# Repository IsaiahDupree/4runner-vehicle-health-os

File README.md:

# 4Runner Vehicle Health OS

Local-first, explainable vehicle-health and maintenance software for a 2005 Toyota 4Runner.

The project has two immutable source baselines: [Vehicle Health OS PRD v0.1](docs/prd/2005_Toyota_4Runner_Vehicle_Health_OS_PRD_v0.1.docx) and [Telemetry Build Master Spec v1](docs/prd/4Runner_Telemetry_Build_Master_Spec.docx). Their joined authority and unique requirement namespaces are defined in the [master project specification](docs/prd/MASTER-PROJECT-SPEC.md). The later [focused A/C telemetry source record](docs/prd/AC-TELEMETRY-SOURCE.md) controls the A/C node where it is more specific. The governing invariant is:

> raw observation -> decoded signal -> feature -> versioned equation -> calculation run -> finding -> recommendation -> service/inspection -> new lifecycle baseline

No derived value is authoritative unless that lineage can be reconstructed.

## Current baseline

E0 plus the first native iOS control slice are implemented here:

- stable typed domain IDs;
- versioned JSON Schemas for evidence, signals, captures, equations, calculations, and AI claims;
- a protobuf source contract and fixed transport-frame decision for mobile/ESP32 interoperability;
- deterministic simulator capture bundles with hashes and manifests;
- an A/C bench-sweep capture/replay path, A/C node telemetry and POST contracts, and evidence-bound pressure-lift, pressure-ratio, and vent-delta calculations;
- offline replay with integrity, sequence, timestamp, and schema validation;
- a versioned passive-CAN discovery analyzer that reports acquisition facts, sampling coverage,
  raw activity, checksum candidates, and correlations without assigning unverified vehicle meanings;
- a source-pinned 2005 4Runner passive-CAN hypothesis pack and real-corpus evaluator that exposes
  candidate fields, conflicting transforms, limitations, and validation gates while keeping the
  accepted signal count at zero;
- an immutable eight-session/5,176-record real-CAN replay corpus with SHA-256 provenance, clean and
  faulted live/history reconstruction, and production-decoder load tests in Python, Swift, and Kotlin;
- self-resynchronizing mobile stream decoders that surface discarded/corrupt transport bytes and
  recover later valid frames without converting communication faults into vehicle-health claims;
- a canonical 15-scenario real-evidence reliability matrix covering 20-cycle soak, MTU churn,
  bursts, duplicates, loss, corruption, reordering, stale link epochs, reconnects, modeled
  supervision timeout, queue overrun, bounded memory, and mixed interference, with aligned Swift
  transport tests and a full Kotlin/on-head-unit implementation;
- per-ECU SAE J1979 supported-PID enumeration, pinned standard read-only value decoding, and an
  iPhone/Android passive-response path that cannot substitute zero for unavailable evidence;
- synchronized Techstream/reference capture plus a candidate-only analyzer for `0x2C4`, `0x025`,
  and `0x2C1` raw fields;
- deterministic passive-CAN archive offload/reload plus an iOS multi-session research chart that
  plots retained evidence, pins pack/hash/validation lineage, and fails closed across app restarts;
- a durable iPhone private-evidence outbox and authenticated append-only receiver/agent claim queue;
- CI checks for schema validity and deterministic replay;
- a Swift 6 core with CRC32C framing, guarded discovery plans, signed firmware verification, OTA preflight, and AI evidence handoff;
- a buildable native SwiftUI app with handshake-verified CoreBluetooth restoration,
  encrypted-bond reconnection, WiCAN factory detection, gateway health, signed semantic experiments,
  private-network OTA, and evidence export;
- a local-first technician diagnostic-case workspace with immutable revisions, typed evidence and
  hypotheses, hash-verified private attachments, verification/void history, and deterministic
  privacy-selected draft reports that cannot mutate canonical maintenance history;
- a signed public Release Hub consumed by iPhone and Android for target-aware Android, OBD ESP32,
  and A/C recovery artifact discovery and verified staging;
- a public WiCAN Pro ESP32-S3 firmware fork with passive/listen-only enforcement, framed BLE health reporting, OTA A/B partitions, and rollback self-tests;
- a physically targeted classic-ESP32/MrDIY firmware with bonded BLE health, passive CAN, persistent
  evidence, A/B rollback, a release-default-off status SoftAP, and explicitly activated signed Wi-Fi
  OTA;
- a backup-first public Web Serial provisioner with target detection, full-flash recovery download, release hashing, installation, and same-capacity restore;
- explicit iOS, legacy Android, gateway firmware, and added-sensor hardware boundaries.

No target-vehicle PID, threshold, service interval, or trim-specific constant is invented in this baseline. Those enter only through independently validated, versioned Vehicle Signal and Configuration Packs.

## Quick start

Requires Python 3.12 or newer.

```bash
python3 -m venv .venv
.venv/bin/python -m pip install -e './tooling[test]'
.venv/bin/vhos contracts check
.venv/bin/vhos simulate --scenario cold-start-idle --output build/captures/cold-start-idle
.venv/bin/vhos validate-bundle build/captures/cold-start-idle
.venv/bin/vhos replay build/captures/cold-start-idle
.venv/bin/vhos simulate --scenario ac-bench-sweep --output build/captures/ac-bench-sweep
.venv/bin/vhos validate-bundle build/captures/ac-bench-sweep
.venv/bin/vhos calculate-ac build/captures/ac-bench-sweep
.venv/bin/vhos discover-can path/to/passive-can-recent-logs.ndjson \
  --output build/can-discovery.report.json
.venv/bin/vhos evaluate-can-hypotheses \
  test-replay/real-can-2026-08-18/sessions \
  --output build/can-signal-hypotheses.report.json
.venv/bin/vhos validate-can-replay-corpus test-replay/real-can-2026-08-18
.venv/bin/vhos replay-can-corpus test-replay/real-can-2026-08-18 \
  --mode live --repeat 20 --fault clean
.venv/bin/vhos replay-can-corpus test-replay/real-can-2026-08-18 \
  --mode history --fault drop-fragment --fault-interval 257
.venv/bin/vhos test-link-reliability test-replay/real-can-2026-08-18 \
  --soak-cycles 20 --output build/link-reliability-matrix.json
.venv/bin/vhos decode-j1979 path/to/j1979-responses.ndjson \
  --supported-output build/j1979-supported.json \
  --samples-output build/j1979-standard-samples.ndjson
.venv/bin/vhos correlate-can-reference \
  --can path/to/passive-can.ndjson \
  --reference path/to/synchronized-reference-samples.csv \
  --output build/can-reference-candidates.json
.venv/bin/python -m pytest
```

The simulator namespace is deliberately separate from live vehicle data. It creates deterministic engineering evidence for automated tests; it never represents itself as a Toyota measurement.

## Gateway provisioning

- Signed release catalog: [VHOS Release Hub](https://github.com/IsaiahDupree/4runner-vhos-release-hub/releases/latest)
- Public installer: [VHOS Gateway Provisioner](https://vhos-gateway-provisioner.isaiahdupree.chatgpt.site)
- Public firmware source: [IsaiahDupree/4runner-vhos-firmware](https://github.com/IsaiahDupree/4runner-vhos-firmware)
- Development release and recovery evidence: [v0.1.0-dev.1](https://github.com/IsaiahDupree/4runner-vhos-firmware/releases/tag/v0.1.0-dev.1)
- Hardware/software baseline: [recommended hardware](docs/hardware/RECOMMENDED-HARDWARE.md) and [software baseline](docs/hardware/SOFTWARE-BASELINE.md)
- SoftAP incident and default-off activation decision: [2026-08-16 record](docs/development/ESP32-SOFTAP-ACTIVATION-INCIDENT-2026-08-16.md)
- One-command pre-car contracts/build/reset/app-death suite and true-power boundary: [BLE fault-injection plan](docs/development/BLE-FAULT-INJECTION-TEST-PLAN.md)
- Capture-export disconnect and dev28/dev29 recovery: [2026-08-18 incident](docs/development/BLE-CAPTURE-SYNC-DISCONNECT-INCIDENT-2026-08-18.md)

The first installation and recovery path uses a desktop Chrome or Edge browser, USB-C data, and Web
Serial. The browser requires a full-flash backup before it installs the merged image. The iPhone OTA
software path is implemented, but vehicle installation remains locked until deterministic PARKED
and gateway-supply evidence plus the physical backup/upload/power-loss/rollback/restore matrix pass.
See [iPhone to ESP32 Wi-Fi OTA](docs/development/IPHONE-TO-ESP32-WIFI-OTA.md).
The stable device labels and separation from transport identifiers are defined in
[the device naming contract](docs/development/DEVICE-NAMING-CONTRACT.md).

## Repository map

| Path | Responsibility |
| --- | --- |
| `docs/prd/` | Immutable product baseline and source integrity record |
| `docs/architecture/decisions/` | Accepted technical decisions and invariants |
| `contracts/jsonschema/v1/` | Authoritative serialized domain contracts |
| `contracts/proto/v1/` | Mobile/ESP32 payload source contract |
| `equations/v1/` | Immutable A/C equation definitions with applicability and truth boundaries |
| `tooling/` | Contract validator, simulator, bundle writer, and replay engine |
| `tests/` | Contract, determinism, corruption, ordering, and replay tests |
| `test-replay/` | Immutable real-capture corpora and cross-platform replay provenance |
| `ios/` | Native iOS app, portable Swift core, and deterministic XcodeGen project |
| `web-flasher/` | Public backup-first ESP32-S3 installer and recovery UI |
| `android/` | Preserved original Android module boundary; not the primary client after ADR-0003 |
| `firmware/` | Shared ESP32 component boundaries and read-only safety policy |
| `vehicle-signal-packs/` | Accepted signal/configuration packs plus separately contracted, discovery-only hypothesis packs that cannot feed owner health |

Related public repositories keep runtime ownership separate: Android head unit
[`4runner-vhos-android`](https://github.com/IsaiahDupree/4runner-vhos-android) ([download the current `0.1.0-dev.16` APK](https://github.com/IsaiahDupree/4runner-vhos-android/releases/download/android-v0.1.0-dev.16/app-debug.apk)), OBD firmware
[`4runner-vhos-firmware`](https://github.com/IsaiahDupree/4runner-vhos-firmware), A/C firmware
[`4runner-ac-telemetry-node`](https://github.com/IsaiahDupree/4runner-ac-telemetry-node), and the
signed catalog/portal [`4runner-vhos-release-hub`](https://github.com/IsaiahDupree/4runner-vhos-release-hub).

## Development order

1. E1: iOS append-only local truth store and lifecycle ledger; the gateway contract client is now scaffolded.
2. E2: physically verify the published WiCAN Pro VHOS foundation, then add passive capture and constrained discovery without widening the transmit boundary.
3. E3: iOS ingest, reconnect/deduplication, raw persistence, and replay adapter.
4. E4: verified generic OBD baseline plus target-vehicle signal discovery and validation.
5. E5/E6: maintenance schedule and equation/lineage engines before owner-facing scoring.

See [E0 implementation record](docs/delivery/E0-IMPLEMENTATION.md) for the exact backlog and acceptance mapping.
The current saved-vehicle evidence and strict UI interpretation boundary are recorded in the
[CAN discovery display baseline](docs/development/CAN-DISCOVERY-DISPLAY-BASELINE-2026-08-18.md).
The device-free sustained-load, corruption, fragmentation, disconnect, and Android historical
replay workflow is recorded in
[the real-CAN replay record](docs/development/REAL-CAN-REPLAY-AND-LOAD-TESTING-2026-08-18.md).
The 15-condition cross-device impairment matrix, acceptance budgets, Android reliability UI, and
remaining hardware-in-loop gates are recorded in
[the cross-device reliability lab](docs/development/CROSS-DEVICE-RELIABILITY-LAB-2026-08-18.md).
The supported-PID, synchronized Toyota-reference, and private-outbox implementation is recorded in
[the August 18 J1979/evidence delivery](docs/development/J1979-REFERENCE-VALIDATION-AND-PRIVATE-OUTBOX-2026-08-18.md).
The current source-pinned Toyota signal candidates, corpus results, interpretation boundaries, and
minimum validation session are recorded in
[the CAN signal interpretation record](docs/development/CAN-SIGNAL-INTERPRETATION-2026-08-18.md).
The latest iPhone-export verification, primary-source research update, candidate ranking, Android
display boundary, and next labeled-capture procedure are recorded in
[the 2026-08-20 CAN evidence and research update](docs/development/CAN-EVIDENCE-RESEARCH-UPDATE-2026-08-20.md).
The real-evidence iPhone chart, fresh-session archive reload gate, exact candidate fields, and
owner-health authority lock are recorded in
[the iOS retained CAN research implementation](docs/development/IOS-RETAINED-CAN-RESEARCH-GRAPHS-2026-08-20.md).
The play/pause/scrub/speed/loop transport, progressive exact-point graph, session-boundary display,
and real multi-session acceptance suite are recorded in
[the iOS retained CAN playback lab](docs/development/IOS-RETAINED-CAN-PLAYBACK-LAB-2026-08-20.md).

The authority-separated physical-unit candidates, derived statistics, rotational comparison, and
cross-platform presentation rules are recorded in [the CAN units view](docs/development/CAN-UNITS-NOTE-2026-08-28.md).

The authority boundary and delivered local iOS technician workflow are recorded in
[ADR-0005](docs/architecture/decisions/0005-technician-diagnostic-case-drafts.md) and the
[mechanic diagnostic-case implementation record](docs/development/MECHANIC-DIAGNOSTIC-CASE-MVP-2026-09-07.md).

Run the complete copied-iPhone evidence recovery, delta analysis, candidate
mapping, replay, and 15-scenario link stress lab with one command using
[the offline field-return runbook](docs/development/OFFLINE-FIELD-RETURN-ONE-SHOT.md).
Run that analysis together with all shared, Swift/iOS Simulator, and Android
desktop gates—without contacting any physical device—using
[the device-free field-return acceptance runner](docs/development/DEVICE-FREE-FIELD-RETURN-ACCEPTANCE.md).
The governing unknown-by-default whole-vehicle model, head-unit inventory contract, 2005 4Runner
configuration guard, and evidence-basis separation are recorded in
[the whole-vehicle digital-twin foundation](docs/development/WHOLE-VEHICLE-DIGITAL-TWIN-FOUNDATION-2026-08-18.md).
The cross-platform Connect → Discover → Test → Capture → Validate → Promote workflow, platform
roles, authority states, session records, fail-closed promotion gate, and first production slice are
defined in
[the Discovery subsystem architecture](docs/development/DISCOVERY-SUBSYSTEM-ARCHITECTURE-2026-08-21.md).
The Android vendor-stack discovery fallback, one-client iPhone/Android handoff, connected-launch
recovery, and explicitly owner-acknowledged local evidence-only selector workflow are recorded in
[the BLE/local-evidence runbook](docs/development/BLE-DISCOVERY-CONNECTED-LAUNCH-AND-LOCAL-EVIDENCE-2026-08-24.md).
The exact offline capture-finalization and experimental-candidate persistence boundary—and the
remaining reason the registration button stays disabled—are recorded in
[the offline candidate-registration gap](docs/development/OFFLINE-CANDIDATE-REGISTRATION-GAP-2026-08-24.md).

## Safety boundary

- Production gateway startup is passive/listen-only.
- There is no arbitrary CAN-transmit command in the shared contract.
- Any diagnostic request references a firmware-resident allowlist entry; iOS does not supply raw request bytes.
- Active Tests, vehicle control, ECU flashing, and code clearing are outside MVP scope.
- Gateway health/data loss is never presented as vehicle failure.

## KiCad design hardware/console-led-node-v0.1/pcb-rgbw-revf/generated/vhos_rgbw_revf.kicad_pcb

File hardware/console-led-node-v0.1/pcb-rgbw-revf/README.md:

# Rev F single-board 4Runner RGBW controller

One four-layer PCB carries the ESP32-S3, automotive input-protection circuit,
two replaceable MINI fuses, TAIL and DIM sensing, and four RGBW drivers. The
2005 4Runner V8's six-pin Toyota IR1 loom provides switched 12 V and ground
through a single branch cable. The other cable goes to the RGBW pod. The
existing CAN ESP32 is the wireless telemetry source. The lighting firmware
and head-unit relay still need physical integration.
[IR1 factory diagrams](../connector-adapter/IR1-WIRE-PLAN.md) ·
[Pinned CAN gateway firmware](https://github.com/IsaiahDupree/4runner-vhos-firmware/tree/a523483abc984a406c73659653571198e46b04a0/targets/mrdiy-esp32-v13).

## Files

| Use | Files |
| --- | --- |
| PCB editing | [KiCad project](generated/vhos_rgbw_revf.kicad_pro) · [PCB](generated/vhos_rgbw_revf.kicad_pcb) · [Schematic](generated/vhos_rgbw_revf.kicad_sch) · [Schematic PDF](generated/schematic.pdf) |
| PCB fabrication and assembly pricing | [Gerbers and drills](generated/4Runner_RGBW_RevF_Gerbers.zip) · [JLCPCB BOM](jlcpcb/BOM.csv) · [JLCPCB CPL](jlcpcb/CPL.csv) · [Component costs and stock](jlcpcb/README.md) |
| PCB and enclosure CAD | [PCB STEP](generated/4Runner_RGBW_RevF_PCB.step) · [FreeCAD assembly](generated/4Runner_RevF_Assembly.FCStd) · [Toyota wire STEP](generated/4Runner_RevF_Toyota_Wires.step) |
| Case and fit coupons | [Base STL](generated/case_base.stl) · [Lid STL](generated/case_lid.stl) · [Cable entry](generated/front_ports_coupon.stl) · [Lid section](generated/front_lid_coupon.stl) · [M3 inserts](generated/m3_tolerance_coupon.stl) |
| Wiring and checks | [Wire register](WIRE-REGISTER.csv) · [Harness and case hardware](HARNESS-AND-CASE.csv) · [Verification](generated/verification.json) · [Bench test sequence](BENCH.md) |

## Wire register

| Toyota or board position | Installed on Rev F |
| --- | --- |
| IR1-5 white/black | J1-1 GND |
| IR1-6 pink/blue | J1-2 switched ACC through the 3 A main fuse |
| IR1-1 green | J1-3 TAIL to ESP32 GPIO5 through a protected sense circuit |
| IR1-2 white/green | J1-4 DIM to ESP32 GPIO4 through a protected sense circuit |
| IR1-3 green | Factory lighter ring circuit plus labeled, insulated TAIL reserve tail on the tee |
| IR1-4 white/green | Factory dimmer return plus labeled, insulated DIM reserve tail on the tee |
| J2-1 through J2-5 | R−, G−, B−, protected common +12 V, W− |

Wire the external tee 1:1 across all six cavities where the factory mate is
fitted. Keep the two capped reserve tails accessible outside the case. Verify
cavity numbers because the TAIL and DIM pairs share colors. Measure the actual
pod's five contacts and load before attaching it. The table numbers refer to
the PCB's J2 pads. [Connector face and meter checks](../connector-adapter/IR1-WIRE-PLAN.md#mating-face-reference).

## Power and programming

- F1 is **3 A, 58 V DC** on the main and LED feed. F2 is **1 A, 32 V DC**
  on the protected logic branch. LEDs draw from the protected vehicle feed.
  The LM5164-Q1 feeds the gate drivers and 3.3 V buck. The calculated startup
  threshold is 7.83–8.83 V at the protected buck input. An ACC feed that drops
  during cranking can reset the controller. [Rail and input calculations](generated/electrical-screen.json).
- The 3.3 V regulator targets 3.384 V. The ESP32 supervisor holds EN low until
  startup and on brownout. GPIO18, 17, 14 and 2 drive R, G, B and W. GPIO21
  enables the drivers. The TAIL/DIM inputs now use 18 kΩ ADC series resistors.
  Expect roughly 0.99 V at a settled 14.4 V input. Calibrate the actual divider
  and console dimmer waveform on the bench. [Sense and reset calculations](generated/electrical-screen.json).
- Flash with a 3.3 V logic UART while the truck and pod are unplugged and
  J1 is fed by a current-limited bench supply. TP9 is GND. TP10 TX connects to
  adapter RX and TP11 RX to adapter TX. Hold TP12 BOOT low and pulse TP13 EN
  low, then release EN before BOOT. TP14 measures 3.3 V. Leave the adapter's
  power wire disconnected. [Espressif download mode](https://docs.espressif.com/projects/esptool/en/latest/esp32s3/advanced-topics/boot-mode-selection.html).

## Fit and verification

The case measures 164 × 76 × 39.2 mm overall, including the mounting ears.
A 2.8 mm floor and four 2.3 mm lid recesses reduce solid CAD volume by
6.3% with 3.2 mm at the lid rim. The cable saddles, ribs and insert locations
are retained. The lid opens for fuse puller and probe access. For a JLC3DP
nylon print, quote the two STLs and check the sleeve and heat-set insert on
a coupon in the quoted process. The printer simulation uses the FLSUN V400
profile with supports disabled. [Case checks](generated/mechanical-observation.json) ·
[Cura slice receipt](generated/support-free.json) ·
[JLC3DP SLS nylon](https://jlc3dp.com/help/article/3201pa-f-nylon).

The TDK inductor, onsemi diodes and LM74800-Q1 use dimensioned maximum
envelopes in the 3D assembly. The inductor and diode footprints use their
manufacturer land patterns. KiCad verified zero ERC, DRC, unconnected and
schematic parity findings. FreeCAD passed 34 fit checks, 92 wire and
strain-relief checks, and eight screw and insert tool paths. Both case
pieces and all three coupons sliced with support generation off.
[TDK dimensions](https://product.tdk.com/en/system/files/dam/doc/product/inductor/inductor/smd/catalog/inductor_automotive_power_spm6545vt-d_en.pdf) ·
[onsemi CASE 477](https://www.onsemi.com/download/package-drawing/pdf/477-02.pdf) ·
[TI DRR0012E package](https://www.ti.com/lit/ds/symlink/lm7480-q1.pdf).

The parts and geometry are for an evaluation prototype. Bench power,
cold-pulse response, full LED load, actual inserts and sleeve retention,
RF range and installed Toyota fit are still to be measured.
[Bench sequence and acceptance points](BENCH.md).

Regenerate on Orion from [pcb-rgbw-revb](../pcb-rgbw-revb) with
`python3 -B orion_client.py start UNIQUE-ID --stage toyota-rev-f`.
Use `status`, `fetch` and `stop` with the same identity.

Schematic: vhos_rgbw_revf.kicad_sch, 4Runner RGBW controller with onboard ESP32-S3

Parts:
C1: 10u 63V EEEFK1J100P; CP_Elec_6.3x5.8; MPN EEEFK1J100P
C2, C3: 2.2u 100V X7R; C_1210_3225Metric; MPN CL32B225KCJVPJE
C4: 2.2n 50V X7R; C_0603_1608Metric; MPN 0603B222K500NT
C5: 3.3n 50V X7R; C_0603_1608Metric; MPN CL10B332KB8NNNC
C6: 180p C0G; C_0603_1608Metric; MPN CL10C181JB8NNNC
C7, C8: 22u 25V X7R; C_1210_3225Metric; MPN MCAST32MSB7226KPNA01
C9, C11: 100n 25V X7R; C_0603_1608Metric; MPN CC0603KRX7R9BB104
C10, C12, C26: 1u 25V X7R; C_0603_1608Metric; MPN CL10B105KA8NNNC
C13, C14: 100n 100V X7R; C_0805_2012Metric; MPN CL21B104KCFNNNE
C15, C25: 100n 50V X7R; C_0603_1608Metric; MPN CC0603KRX7R9BB104
C16: 10n 100V X7R; C_0805_2012Metric; MPN GRM21BR72A103KA01L
C17: 47u 50V; CP_Elec_8x6.2; MPN EEEFK1H470P
C18, C19, C20, C21: 100n 50V; C_0603_1608Metric; MPN CC0603KRX7R9BB104
C22, C23, C24: 22u 16V X7R; C_1206_3216Metric; MPN EMK316BB7226ML-T
D1: SMBJ28CAQ; D_SMB; MPN SMBJ28CAQ-13-F
D3, D4, D5, D6: SMBJ24CA; D_SMB; MPN SMBJ24CAQ-13-F
D7, D8: NSVBAT54HT1G; onsemi_SOD-323_477; MPN NSVBAT54HT1G
F1: 3A MINI MAIN / LED; Keystone_3568_MINI_Vertical; MPN 3568
F2: 1A MINI LOGIC; Keystone_3568_MINI_Vertical; MPN 3568
J1: TOYOTA IR1 IN; Toyota_IR1_4_Pads
J2: RGBW OUT; RGBW_Output_5_Pads
L1: 68u 20% TDK; TDK_SPM6545VT-D; MPN SPM6545VT-680M-D
L2: 2.2uH; L_Bourns-SRN4018; MPN SRN4018-2R2M
MH1, MH2, MH3, MH4: M3 CASE SUPPORT; MountingHole_3.2mm_M3; MPN PCB FEATURE
Q1, Q2, Q3, Q4: BUK9Y15-60E; LFPAK56; MPN BUK9Y15-60E,115
Q5, Q6: BUK9Y19-100E; LFPAK56; MPN BUK9Y19-100E,115
R1: 39k 1%; R_0603_1608Metric; MPN 0603WAF3902T5E
R2: 1M; R_0603_1608Metric; MPN 0603WAF1004T5E
R3: 220k 1%; R_0603_1608Metric; MPN 0603WAF2203T5E
R4: 150k 1%; R_0603_1608Metric; MPN 0603WAF1503T5E
R5: 47k 1%; R_0603_1608Metric; MPN 0603WAF4702T5E
R6: 68k 1%; R_0603_1608Metric; MPN 0603WAF6802T5E
R7, R17, R18, R19, R20: 100k; R_0603_1608Metric; MPN 0603WAF1003T5E
R8: 2.2k; R_0603_1608Metric; MPN 0603WAF2201T5E
R9, R10, R11, R12: 100; R_0603_1608Metric; MPN 0603WAF1000T5E
R13, R14, R15, R16, R36, R37, R38: 10k; R_0603_1608Metric; MPN 0603WAF1002T5E
R21, R34: 46.4k 0.1%; R_0603_1608Metric; MPN RT0603BRD0746K4L
R22: 4.02k 0.1%; R_0603_1608Metric; MPN RT0603BRD074K02L
R23: 100R; R_0603_1608Metric; MPN 0603WAF1000T5E
R24, R25, R26, R27: 49.9k 0.1%; R_1206_3216Metric; MPN RT1206BRD0749K9L
R28, R29, R32, R33: 22k 0.1%; R_0603_1608Metric; MPN AT0603BRD0722KL
R30, R31: 18k 1%; R_0603_1608Metric; MPN 0603WAF1802T5E
R35: 10k 1%; R_0603_1608Metric; MPN 0603WAF1002T5E
TP5: V5_LOGIC; TestPoint_Pad_D1.0mm; MPN PCB FEATURE
TP6: GND; TestPoint_Pad_D1.0mm; MPN PCB FEATURE
TP7: PGOOD; TestPoint_Pad_D1.0mm; MPN PCB FEATURE
TP8: ENABLE_REQ; TestPoint_Pad_D1.0mm; MPN PCB FEATURE
TP9: GND; TestPoint_Pad_D1.5mm; MPN PCB FEATURE
TP10: UART_TX; TestPoint_Pad_D1.5mm; MPN PCB FEATURE
TP11: UART_RX; TestPoint_Pad_D1.5mm; MPN PCB FEATURE
TP12: BOOT_N; TestPoint_Pad_D1.5mm; MPN PCB FEATURE
TP13: CHIP_EN; TestPoint_Pad_D1.5mm; MPN PCB FEATURE
TP14: ESP_3V3; TestPoint_Pad_D1.5mm; MPN PCB FEATURE
U1: LM5164QDDARQ1; HSOP-8-1EP_3.9x4.9mm_P1.27mm_EP2.41x3.1mm; MPN LM5164QDDARQ1
U2, U3: UCC27524AQDRQ1; SOIC-8_3.9x4.9mm_P1.27mm; MPN UCC27524AQDRQ1
U4: LM74800-Q1; WSON-12-1EP_3x3mm_P0.5mm_EP1.5x2.5mm; MPN LM74800QDRRRQ1
U5: SN3257-Q1; TSSOP-16_4.4x5mm_P0.65mm; MPN SN3257QPWRQ1
U6, U7: LM4040 2.5V; SOT-23; MPN LM4040C25QFTA
U8: TLV809E 2.93V; SOT-23; MPN TLV809ED29DBZR
U9: TLV62569DBVR; SOT-23-5; MPN TLV62569DBVR
U10: TLV803EC30DBZR; SOT-23; MPN TLV803EC30DBZR
U11: ESP32-S3-WROOM-1-N16R8; ESP32-S3-WROOM-1; MPN ESP32-S3-WROOM-1-N16R8

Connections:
/ACC_FUSED: C13.1, D1.1, F1.2, Q5.1, Q5.2, Q5.3, U4.2 (A), U4.3 (VSNS)
/BOOT_N: R37.2, TP12.1, U11.27 (IO0)
/BST: C4.1, U1.7 (BST)
/CAP_PUMP: C15.1, U4.11 (CAP)
/CHIP_EN: C26.1, R36.2, TP13.1, U10.1 (RESET_N), U11.3 (EN)
/DGATE: Q5.4, U4.1 (DGATE)
/DIM_ADC: C20.1, R31.2, R33.1, U11.4 (IO4)
/DIM_CLAMP: D8.1 (K), R27.2, R29.1, U5.6 (S2B), U7.1 (K)
/DIM_RETURN: J1.4 (IR1-2), R26.1
/DIM_SERIES: R26.2, R27.1
/DIM_SW: R31.1, U5.7 (D2)
/DOWNLOAD_STRAP: R38.1, U11.16 (IO46)
/DRV_B: R11.1, U3.7 (OUTA)
/DRV_G: R10.1, U2.5 (OUTB)
/DRV_R: R9.1, U2.7 (OUTA)
/DRV_W: R12.1, U3.5 (OUTB)
/ENABLE_REQ: R8.1, TP8.1, U2.1 (ENA), U2.8 (ENB), U3.1 (ENA), U3.8 (ENB), U11.23 (IO21)
/ESP_3V3: C18.1, C21.1, C23.1, C24.1, C25.1, L2.2, R34.1, R36.1, R37.1, TP14.1, U5.16 (VDD), U8.3 (VDD), U10.3 (VDD), U11.2 (3V3)
/FB: C6.2, R4.2, R5.1, U1.5 (FB)
/FB_3V3: R34.2, R35.1, U9.5 (FB)
/GATE_B: Q3.4 (G), R11.2, R15.1
/GATE_G: Q2.4 (G), R10.2, R14.1
/GATE_R: Q1.4 (G), R9.2, R13.1
/GATE_W: Q4.4 (G), R12.2, R16.1
/GND: C1.2, C2.2, C3.2, C7.2, C8.2, C9.2, C10.2, C11.2, C12.2, C13.2, C14.2, C16.2, C17.2, C18.2, C19.2, C20.2, C21.2, C22.2, C23.2, C24.2, C25.2, C26.2, D1.2, D3.2, D4.2, D5.2, D6.2, D7.2 (A), D8.2 (A), J1.1 (IR1-5), Q1.1 (S1), Q1.2 (S2), Q1.3 (S3), Q2.1 (S1), Q2.2 (S2), Q2.3 (S3), Q3.1 (S1), Q3.2 (S2), Q3.3 (S3), Q4.1 (S1), Q4.2 (S2), Q4.3 (S3), R1.2, R3.2, R5.2, R8.2, R13.2, R14.2, R15.2, R16.2, R17.2, R18.2, R19.2, R20.2, R22.2, R28.2, R29.2, R32.2, R33.2, R35.2, R38.2, TP6.1, TP9.1, U1.1 (GND), U1.9 (EP_GND), U2.3 (GND), U3.3 (GND), U4.7 (GND), U5.2 (S1A), U5.5 (S2A), U5.8 (GND), U5.9 (D3), U5.10 (S3B), U5.11 (S3A), U5.12 (D4), U5.13 (S4B), U5.14 (S4A), U5.15 (EN_N), U6.2 (A), U6.3 (A/NC), U7.2 (A), U7.3 (A/NC), U8.2 (GND), U9.2 (GND), U10.2 (GND), U11.1 (GND), U11.40 (GND), U11.41 (EPAD)
/HGATE: Q6.4, R23.1, U4.8 (HGATE)
/INRUSH: C16.1, R23.2
/LED_B_NEG: D5.1, J2.3, Q3.5 (D_MB)
/LED_G_NEG: D4.1, J2.2, Q2.5 (D_MB)
/LED_POS: C17.1, F2.1, J2.4, Q6.1, Q6.2, Q6.3, U4.9 (OUT)
/LED_R_NEG: D3.1, J2.1, Q1.5 (D_MB)
/LED_W_NEG: D6.1, J2.5, Q4.5 (D_MB)
/OV_FEED: R21.1, U4.4 (SW)
/OV_SENSE: R21.2, R22.1, U4.5 (OV)
/PGOOD: R7.2, TP7.1, U1.6 (PGOOD)
/POWER_MID: C14.1, C15.2, Q5.5, Q6.5, U4.6 (EN/UVLO), U4.10 (VS), U4.12 (C)
/PWM_B: R19.1, U3.2 (INA), U11.22 (IO14)
/PWM_G: R18.1, U2.4 (INB), U11.10 (IO17)
/PWM_R: R17.1, U2.2 (INA), U11.11 (IO18)
/PWM_W: R20.1, U3.4 (INB), U11.38 (IO2)
/RIPPLE: C5.1, C6.1, R6.2
/RON: R1.1, U1.4 (RON)
/SENSE_READY: U5.1 (SEL), U8.1 (RESET_N)
/SW: C4.2, L1.1, R6.1, U1.8 (SW)
/SW_3V3: L2.1, U9.3 (SW)
/TAIL_12V: J1.3 (IR1-1), R24.1
/TAIL_ADC: C19.1, R30.2, R32.1, U11.5 (IO5)
/TAIL_CLAMP: D7.1 (K), R25.2, R28.1, U5.3 (S1B), U6.1 (K)
/TAIL_SERIES: R24.2, R25.1
/TAIL_SW: R30.1, U5.4 (D1)
/UART_RX: TP11.1, U11.36 (RXD0)
/UART_TX: TP10.1, U11.37 (TXD0)
/UVLO: R2.2, R3.1, U1.3 (EN_UVLO)
/V5_LOGIC: C5.2, C7.1, C8.1, C9.1, C10.1, C11.1, C12.1, C22.1, L1.2, R4.1, R7.1, TP5.1, U2.6 (VDD), U3.6 (VDD), U9.1 (EN), U9.4 (VIN)
/VEH_ACC: F1.1, J1.2 (IR1-6)
/VIN_PROT: C1.1, C2.1, C3.1, F2.2, R2.1, U1.2 (VIN)

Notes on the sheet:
FUSED INPUT, PROTECTION AND 5 V SUPPLY
VEHICLE INPUT AND CONTROLLER STACK
ONE COMMON-POSITIVE RGBW ZONE
TOYOTA IR1 ILLUMINATION SENSE
ONBOARD ESP32-S3, 3.3 V REGULATOR AND SERVICE PADS
EVALUATION HARDWARE / VERIFY VEHICLE FEED, LED PINOUT AND USB ISOLATION

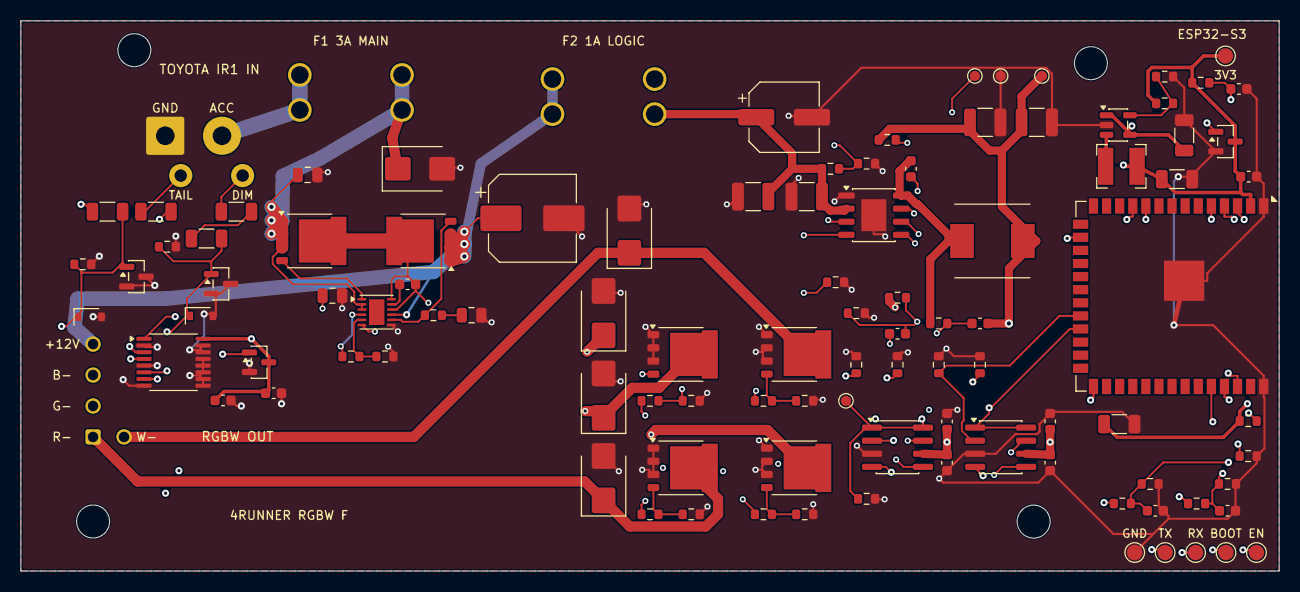
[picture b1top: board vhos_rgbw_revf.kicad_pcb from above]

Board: 4 copper layers, 122.0 x 53.3 mm, 108 parts (0 on the bottom side), 56 nets.

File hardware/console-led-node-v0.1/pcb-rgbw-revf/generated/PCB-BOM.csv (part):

ref,value,mpn,footprint,note,jlcpcb_part
C1,10u 63V EEEFK1J100P,EEEFK1J100P,Capacitor_SMD:CP_Elec_6.3x5.8,"Polar bulk damping candidate; manufacturer 6.3mm diameter, 5.8mm body height. Cable-response/ripple validation pending.",C128459
C2,2.2u 100V X7R,CL32B225KCJVPJE,Capacitor_SMD:C_1210_3225Metric,,C5596903
C3,2.2u 100V X7R,CL32B225KCJVPJE,Capacitor_SMD:C_1210_3225Metric,,C5596903
U1,LM5164QDDARQ1,LM5164QDDARQ1,Package_SO:HSOP-8-1EP_3.9x4.9mm_P1.27mm_EP2.41x3.1mm,"5V logic only; target 0.5A evaluation load, thermal and transient tests pending",C2072225
L1,68u 20% TDK,SPM6545VT-680M-D,VHOS_RevB:TDK_SPM6545VT-D,TDK automotive inductor. Land pattern and maximum envelope from the TDK drawing.,C2047878
R1,39k 1%,0603WAF3902T5E,Resistor_SMD:R_0603_1608Metric,"Uniroyal 0603 thick film, 1%, 0.1 W.",C23153
R2,1M,0603WAF1004T5E,Resistor_SMD:R_0603_1608Metric,"Uniroyal 0603 thick film, 1%, 0.1 W.",C22935
R3,220k 1%,0603WAF2203T5E,Resistor_SMD:R_0603_1608Metric,"Uniroyal 0603 thick film, 1%, 0.1 W.",C22961
R4,150k 1%,0603WAF1503T5E,Resistor_SMD:R_0603_1608Metric,"Uniroyal 0603 thick film, 1%, 0.1 W.",C22807
R5,47k 1%,0603WAF4702T5E,Resistor_SMD:R_0603_1608Metric,"Uniroyal 0603 thick film, 1%, 0.1 W.",C25819
R6,68k 1%,0603WAF6802T5E,Resistor_SMD:R_0603_1608Metric,"Uniroyal 0603 thick film, 1%, 0.1 W.",C23231
C4,2.2n 50V X7R,0603B222K500NT,Capacitor_SMD:C_0603_1608Metric,,C1604
C5,3.3n 50V X7R,CL10B332KB8NNNC,Capacitor_SMD:C_0603_1608Metric,,C1613
C6,180p C0G,CL10C181JB8NNNC,Capacitor_SMD:C_0603_1608Metric,,C17096
C7,22u 25V X7R,MCAST32MSB7226KPNA01,Capacitor_SMD:C_1210_3225Metric,,C5372271
C8,22u 25V X7R,MCAST32MSB7226KPNA01,Capacitor_SMD:C_1210_3225Metric,,C5372271
R7,100k,0603WAF1003T5E,Resistor_SMD:R_0603_1608Metric,"Uniroyal 0603 thick film, 1%, 0.1 W.",C25803
U2,UCC27524AQDRQ1,UCC27524AQDRQ1,Package_SO:SOIC-8_3.9x4.9mm_P1.27mm,5V gate drive; enables have internal pullups overridden by external 2.2k pulldown,C544585
U3,UCC27524AQDRQ1,UCC27524AQDRQ1,Package_SO:SOIC-8_3.9x4.9mm_P1.27mm,5V gate drive; enables have internal pullups overridden by external 2.2k pulldown,C544585
C9,100n 25V X7R,CC0603KRX7R9BB104,Capacitor_SMD:C_0603_1608Metric,,C14663
C11,100n 25V X7R,CC0603KRX7R9BB104,Capacitor_SMD:C_0603_1608Metric,,C14663
C10,1u 25V X7R,CL10B105KA8NNNC,Capacitor_SMD:C_0603_1608Metric,,C29936
C12,1u 25V X7R,CL10B105KA8NNNC,Capacitor_SMD:C_0603_1608Metric,,C29936
R8,2.2k,0603WAF2201T5E,Resistor_SMD:R_0603_1608Metric,"Uniroyal 0603 thick film, 1%, 0.1 W.",C4190
Q1,BUK9Y15-60E,"BUK9Y15-60E,115",Package_TO_SOT_SMD:LFPAK56,"60V; 15mOhm max at 5V gate, 25C. Layout/current ratings remain evaluation targets.",C458196
R9,100,0603WAF1000T5E,Resistor_SMD:R_0603_1608Metric,"Uniroyal 0603 thick film, 1%, 0.1 W.",C22775
R13,10k,0603WAF1002T5E,Resistor_SMD:R_0603_1608Metric,"Uniroyal 0603 thick film, 1%, 0.1 W.",C25804
R17,100k,0603WAF1003T5E,Resistor_SMD:R_0603_1608Metric,"Uniroyal 0603 thick film, 1%, 0.1 W.",C25803
D3,SMBJ24CA,SMBJ24CAQ-13-F,Diode_SMD:D_SMB,Bidirectional output clamp candidate; cable-energy test pending,C1974053
Q2,BUK9Y15-60E,"BUK9Y15-60E,115",Package_TO_SOT_SMD:LFPAK56,"60V; 15mOhm max at 5V gate, 25C. Layout/current ratings remain evaluation targets.",C458196
R10,100,0603WAF1000T5E,Resistor_SMD:R_0603_1608Metric,"Uniroyal 0603 thick film, 1%, 0.1 W.",C22775
R14,10k,0603WAF1002T5E,Resistor_SMD:R_0603_1608Metric,"Uniroyal 0603 thick film, 1%, 0.1 W.",C25804
R18,100k,0603WAF1003T5E,Resistor_SMD:R_0603_1608Metric,"Uniroyal 0603 thick film, 1%, 0.1 W.",C25803
D4,SMBJ24CA,SMBJ24CAQ-13-F,Diode_SMD:D_SMB,Bidirectional output clamp candidate; cable-energy test pending,C1974053
Q3,BUK9Y15-60E,"BUK9Y15-60E,115",Package_TO_SOT_SMD:LFPAK56,"60V; 15mOhm max at 5V gate, 25C. Layout/current ratings remain evaluation targets.",C458196
R11,100,0603WAF1000T5E,Resistor_SMD:R_0603_1608Metric,"Uniroyal 0603 thick film, 1%, 0.1 W.",C22775
R15,10k,0603WAF1002T5E,Resistor_SMD:R_0603_1608Metric,"Uniroyal 0603 thick film, 1%, 0.1 W.",C25804
R19,100k,0603WAF1003T5E,Resistor_SMD:R_0603_1608Metric,"Uniroyal 0603 thick film, 1%, 0.1 W.",C25803
D5,SMBJ24CA,SMBJ24CAQ-13-F,Diode_SMD:D_SMB,Bidirectional output clamp candidate; cable-energy test pending,C1974053
Q4,BUK9Y15-60E,"BUK9Y15-60E,115",Package_TO_SOT_SMD:LFPAK56,"60V; 15mOhm max at 5V gate, 25C. Layout/current ratings remain evaluation targets.",C458196
R12,100,0603WAF1000T5E,Resistor_SMD:R_0603_1608Metric,"Uniroyal 0603 thick film, 1%, 0.1 W.",C22775
R16,10k,0603WAF1002T5E,Resistor_SMD:R_0603_1608Metric,"Uniroyal 0603 thick film, 1%, 0.1 W.",C25804
R20,100k,0603WAF1003T5E,Resistor_SMD:R_0603_1608Metric,"Uniroyal 0603 thick film, 1%, 0.1 W.",C25803
D6,SMBJ24CA,SMBJ24CAQ-13-F,Diode_SMD:D_SMB,Bidirectional output clamp candidate; cable-energy test pending,C1974053
F1,3A MINI MAIN / LED,3568,VHOS_RevB:Keystone_3568_MINI_Vertical,Socket and removable element 0997003.WXN,
F2,1A MINI LOGIC,3568,VHOS_RevB:Keystone_3568_MINI_Vertical,Socket and removable element ATM-1,
U4,LM74800-Q1,LM74800QDRRRQ1,Package_SON:WSON-12-1EP_3x3mm_P0.5mm_EP1.5x2.5mm,Common-drain reverse battery protection and OV cutoff. RTN exposed pad floating.,C3215600
D1,SMBJ28CAQ,SMBJ28CAQ-13-F,Diode_SMD:D_SMB,28 V standoff bidirectional input TVS after the 58 V fuse.,C1975352
Q5,BUK9Y19-100E,"BUK9Y19-100E,115",Package_TO_SOT_SMD:LFPAK56,"100 V reverse-blocking NMOS, source on fused input.",C458229
Q6,BUK9Y19-100E,"BUK9Y19-100E,115",Package_TO_SOT_SMD:LFPAK56,"100 V cutoff NMOS, source on protected output.",C458229
R21,46.4k 0.1%,RT0603BRD0746K4L,Resistor_SMD:R_0603_1608Metric,,C861420
R22,4.02k 0.1%,RT0603BRD074K02L,Resistor_SMD:R_0603_1608Metric,,C705781
R23,100R,0603WAF1000T5E,Resistor_SMD:R_0603_1608Metric,,C22775
C13,100n 100V X7R,CL21B104KCFNNNE,Capacitor_SMD:C_0805_2012Metric,,C28233
C14,100n 100V X7R,CL21B104KCFNNNE,Capacitor_SMD:C_0805_2012Metric,,C28233
C15,100n 50V X7R,CC0603KRX7R9BB104,Capacitor_SMD:C_0603_1608Metric,,C14663
C16,10n 100V X7R,GRM21BR72A103KA01L,Capacitor_SMD:C_0805_2012Metric,,C97925
C17,47u 50V,EEEFK1H470P,Capacitor_SMD:CP_Elec_8x6.2,,C278400
U5,SN3257-Q1,SN3257QPWRQ1,Package_SO:TSSOP-16_4.4x5mm_P0.65mm,A inputs at ground during 3.3 V startup. B inputs selected when the rail supervisor releases.,C1858301
U8,TLV809E 2.93V,TLV809ED29DBZR,Package_TO_SOT_SMD:SOT-23,Keeps both ADC inputs at ground during supply transitions until 3.3 V is valid.,C2864833
R24,49.9k 0.1%,RT1206BRD0749K9L,Resistor_SMD:R_1206_3216Metric,,C706414
R25,49.9k 0.1%,RT1206BRD0749K9L,Resistor_SMD:R_1206_3216Metric,,C706414
R28,22k 0.1%,AT0603BRD0722KL,Resistor_SMD:R_0603_1608Metric,,C5455453
R30,18k 1%,0603WAF1802T5E,Resistor_SMD:R_0603_1608Metric,ADC isolation sets attenuation and keeps GPIO above -0.3 V for a -0.5 V switch output.,C25810
R32,22k 0.1%,AT0603BRD0722KL,Resistor_SMD:R_0603_1608Metric,,C5455453
U6,LM4040 2.5V,LM4040C25QFTA,Package_TO_SOT_SMD:SOT-23,Positive clamp to chassis reference.,C531175
D7,NSVBAT54HT1G,NSVBAT54HT1G,VHOS_RevB:onsemi_SOD-323_477,Negative clamp. Check cold-pulse forward drop on the bench.,C179609
C19,100n 50V,CC0603KRX7R9BB104,Capacitor_SMD:C_0603_1608Metric,,C14663
R26,49.9k 0.1%,RT1206BRD0749K9L,Resistor_SMD:R_1206_3216Metric,,C706414
R27,49.9k 0.1%,RT1206BRD0749K9L,Resistor_SMD:R_1206_3216Metric,,C706414
R29,22k 0.1%,AT0603BRD0722KL,Resistor_SMD:R_0603_1608Metric,,C5455453
R31,18k 1%,0603WAF1802T5E,Resistor_SMD:R_0603_1608Metric,ADC isolation sets attenuation and keeps GPIO above -0.3 V for a -0.5 V switch output.,C25810
R33,22k 0.1%,AT0603BRD0722KL,Resistor_SMD:R_0603_1608Metric,,C5455453
U7,LM4040 2.5V,LM4040C25QFTA,Package_TO_SOT_SMD:SOT-23,Positive clamp to chassis reference.,C531175
D8,NSVBAT54HT1G,NSVBAT54HT1G,VHOS_RevB:onsemi_SOD-323_477,Negative clamp. Check cold-pulse forward drop on the bench.,C179609
C20,100n 50V,CC0603KRX7R9BB104,Capacitor_SMD:C_0603_1608Metric,,C14663
C18,100n 50V,CC0603KRX7R9BB104,Capacitor_SMD:C_0603_1608Metric,,C14663
C21,100n 50V,CC0603KRX7R9BB104,Capacitor_SMD:C_0603_1608Metric,,C14663
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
